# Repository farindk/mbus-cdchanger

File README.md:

# M-Bus CD-Changer Controller

A controller board for standalone use of Alpine M-Bus CD-changers.

I got hold of an old car CD-changer that was originally built into a Mercedes-Benz car.
The car and the radio did not exist anymore, but since CD-changers are cool tech, I was wondering whether I could make it work again.
After some searching, I found that the actual manufacturer of the device is Alpine and that it is controlled by an M-Bus protocol.
The pinout of the connector apparently is proprietary, but it is not too difficult to identify the +12V / GND wires.
Just notice that there is a separate separate wire to the car ignition that also has to be connected to +12V to start it up.

The other wires are for M-Bus and the audio output, each with its own GND.

Fortunately, I found this website that did some reverse engineering of the M-Bus protocol: http://www.hohensohn.info/mbus/
Most of it matched my CD-changer, but several commands simply did not work, thus I could not implement typical CD-player functions like "pause".
I assume that this is a limitation of my specific device, but since I don't have the original radio controller, I cannot say for sure.

## Video

[Demo video](https://www.youtube.com/watch?v=HMd5gL0tslU)

## Building it

For anyone interested in playing along, this repository contains the KiCad files for the PCB. The schematics are basically the voltage-level adapter as shown on http://www.hohensohn.info/mbus/
plus the Atmel microcontroller with a few switches, HD44780 compatible display, and power supply. I use an old 12V plug-in power supply. Note that the PCB has the footprint for a TO-92 7805 regulator for the 5V needed for the uC and display.
However, the TO-92 was a slightly too optimistic choice. When I tried, it immediately dissolved in a white cloud. Thus, a TO-220 should be fitted into it instead.
The LCD used is this one: [PDF datasheet](https://www.lcd-module.de/eng/pdf/doma/dips082e.pdf).
The uC-Board is a cheap [Arduino clone](https://www.amazon.com/Teyleten-Robot-Bootloadered-Development-Microcontroller/dp/B08THVMQ46/).

Because of the minimum ordering quantities, I have a couple of spare PCBs (3 available). Anyone interested can drop me a line and I'll send it to them for postage and packaging.

I removed the suspension mounting of the CD drive since it was worn out after so many years anyways, and I mounted the drive mechanics directly to the case.

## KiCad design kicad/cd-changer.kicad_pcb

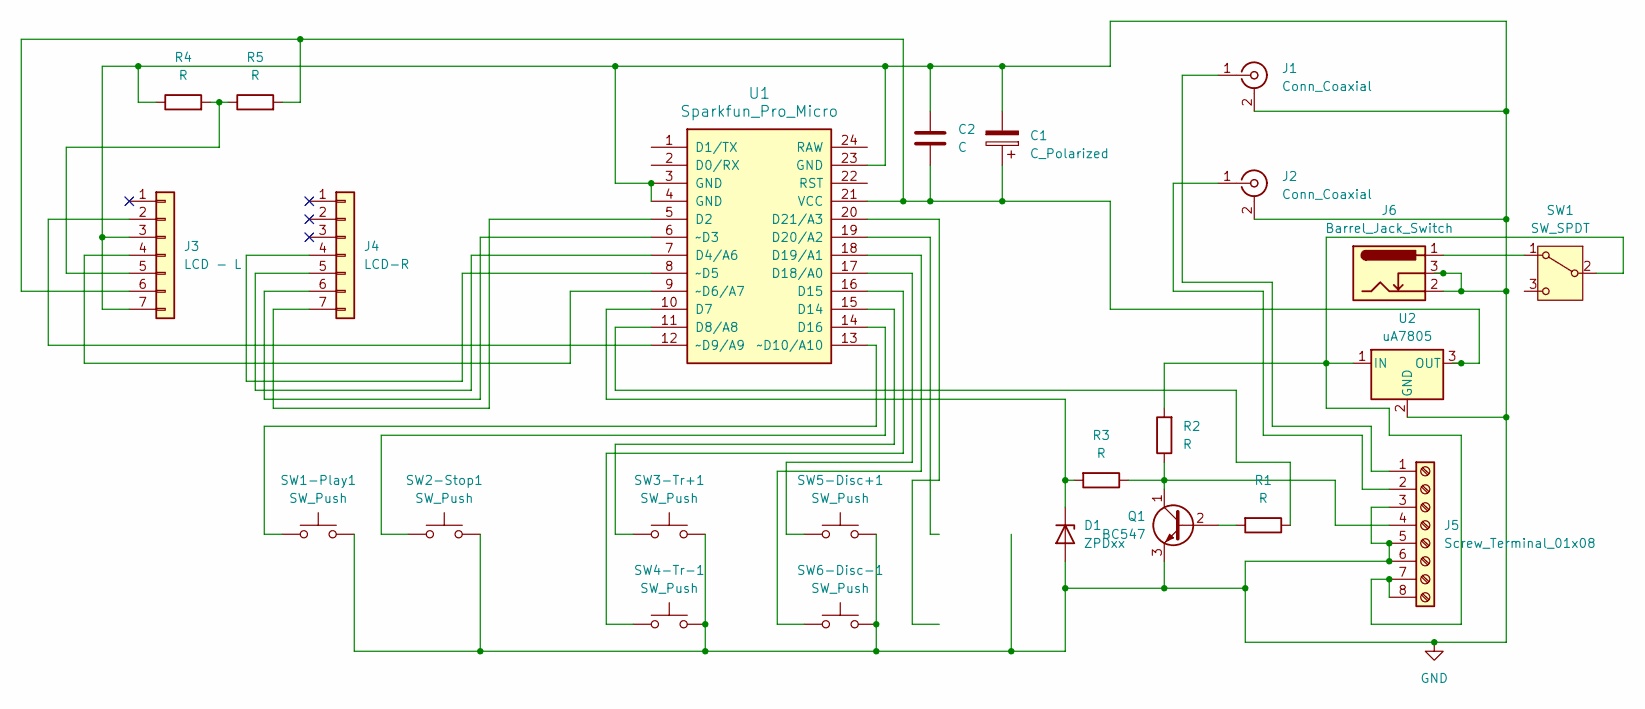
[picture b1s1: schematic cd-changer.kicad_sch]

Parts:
C1: C_Polarized; C_Radial_D10.0mm_H12.5mm_P5.00mm
C2: C; C_Disc_D7.5mm_W5.0mm_P5.00mm
D1: ZPDxx; D_DO-35_SOD27_P10.16mm_Horizontal
J1, J2: Conn_Coaxial; Cinch-Buchse
J3: LCD - L; PinHeader_1x07_P2.54mm_Vertical
J4: LCD-R; PinHeader_1x07_P2.54mm_Vertical
J5: Screw_Terminal_01x08; TerminalBlock_bornier-8_P5.08mm
J6: Barrel_Jack_Switch; BarrelJack_with_switch
Q1: BC547; TO-92_Inline
R1, R2, R3, R4, R5: R; R_Axial_DIN0204_L3.6mm_D1.6mm_P7.62mm_Horizontal
SW1: SW_SPDT; SW_Slide_3pin
SW1-Play1, SW2-Stop1, SW3-Tr+1, SW4-Tr-1, SW5-Disc+1, SW6-Disc-1: SW_Push; SW_PUSH_6mm_H8mm
U1: Sparkfun_Pro_Micro
U2: uA7805; TO-92L_HandSolder

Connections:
GND: C1.2, C2.1, D1.2 (A), J1.2 (Ext), J2.2 (Ext), J3.3, J3.7, J5.3, J5.5, J5.6, J6.2, J6.3, Q1.3 (E), R4.1, SW1-Play1.2, SW2-Stop1.2, SW3-Tr+1.2, SW4-Tr-1.2, SW5-Disc+1.2, SW6-Disc-1.2, U1.3 (GND), U1.4 (GND), U1.23 (GND), U2.2 (GND)
unnamed: D1.1 (K), R3.2, U1.10 (D7)
unnamed: J1.1 (In), J5.1
unnamed: J2.1 (In), J5.2
unnamed: J3.2, U1.12 (~D9/A9)
unnamed: J3.4, U1.9 (~D6/A7)
unnamed: J3.5, R4.2, R5.1
unnamed: C1.1, C2.2, J3.6, R5.2, U1.21 (VCC), U2.3 (OUT)
unnamed: J4.4, U1.8 (~D5)
unnamed: J4.5, U1.7 (D4/A6)
unnamed: J4.6, U1.6 (~D3)
unnamed: J4.7, U1.5 (D2)
unnamed: J5.4, Q1.1 (C), R2.1, R3.1
unnamed: J5.7, J5.8, R2.2, SW1.2 (B), U2.1 (IN)
unnamed: Q1.2 (B), R1.2
unnamed: J6.1, SW1.1 (A)
unnamed: R1.1, U1.11 (D8/A8)
unnamed: SW3-Tr+1.1, U1.15 (D14)
unnamed: SW4-Tr-1.1, U1.16 (D15)
unnamed: SW2-Stop1.1, U1.14 (D16)
unnamed: SW5-Disc+1.1, U1.17 (D18/A0)
unnamed: SW6-Disc-1.1, U1.18 (D19/A1)
unnamed: SW1-Play1.1, U1.13 (~D10/A10)

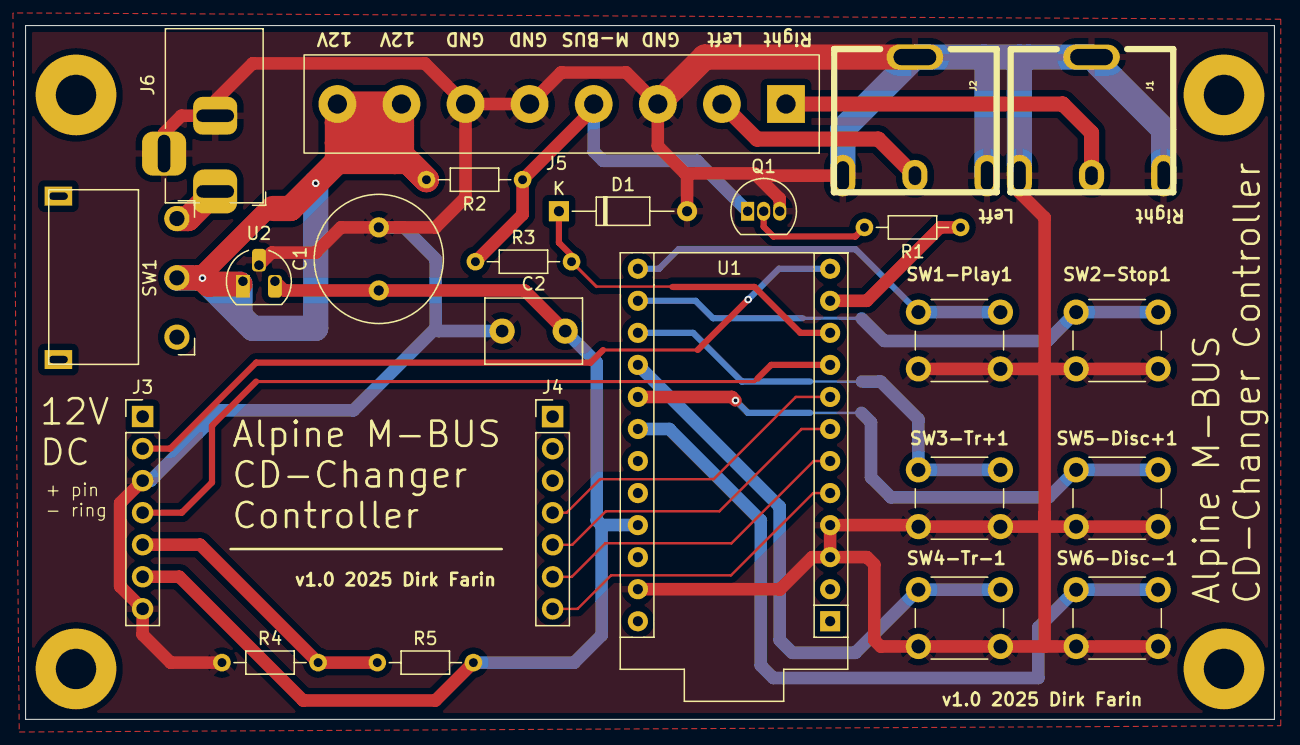
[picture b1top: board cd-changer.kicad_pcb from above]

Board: 2 copper layers, 99.0 x 55.0 mm, 24 parts (0 on the bottom side), 23 nets.

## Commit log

2025-04-14 initial import
2025-04-14 Add link to demo video
